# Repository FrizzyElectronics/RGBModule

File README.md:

# RGBModule
The RGB module is a very simple but useful board. It carries a 5050 RGB LED, with a 4pin connector making it easy to add color to your Arduino projects. It's also a great way to learn about the PWM capabilities of Arduino.

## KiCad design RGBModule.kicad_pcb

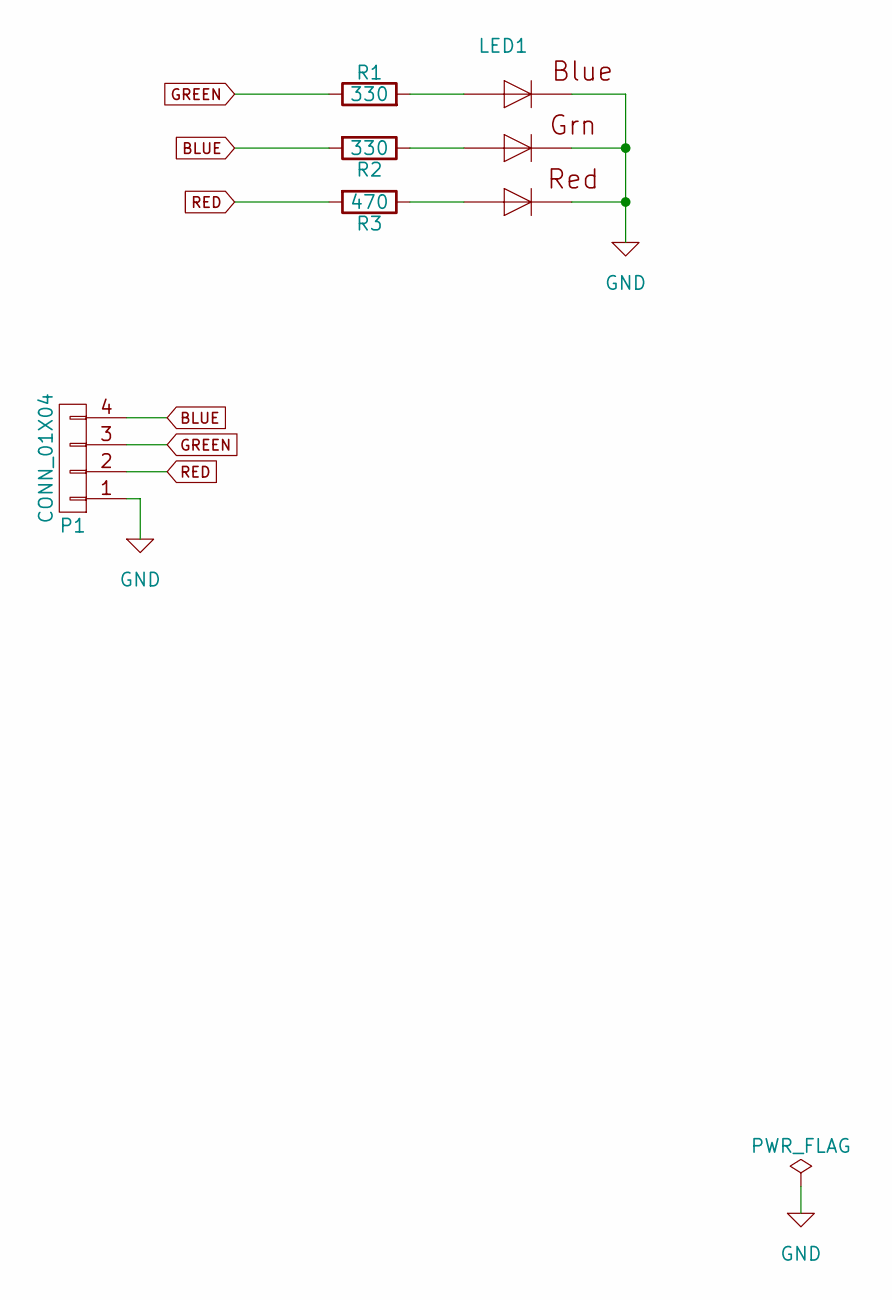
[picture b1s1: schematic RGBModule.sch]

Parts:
LED1: RGBLED5050; LED-TRICOLOR-5050
P1: CONN_01X04; Pin_Header_Angled_1x04_Pitch2.54mm
R1, R2: 330; R_0805
R3: 470; R_0805

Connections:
BLUE: P1.4, R2.2
GND: LED1.4 (BLUE_C), LED1.5 (RED_C), LED1.6 (GREEN_C), P1.1
GREEN: P1.3, R1.1
unnamed: LED1.1 (GREEN_A), R2.1
unnamed: LED1.2 (RED_A), R3.1
unnamed: LED1.3 (BLUE_A), R1.2
RED: P1.2, R3.2

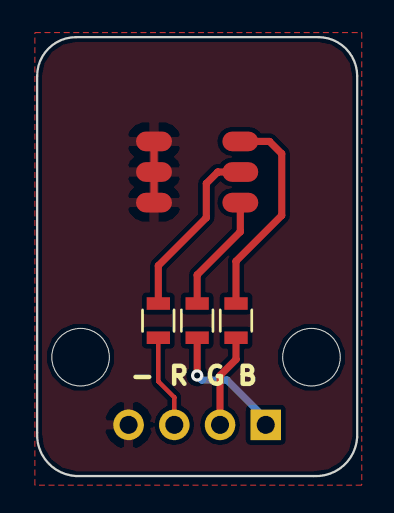
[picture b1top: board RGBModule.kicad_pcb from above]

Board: 2 copper layers, 17.8 x 24.4 mm, 5 parts (0 on the bottom side), 7 nets.

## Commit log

2017-05-22 License Added
2017-05-22 Esquema terminado
2017-05-22 Netlist y footprints asociados
2017-05-22 3D terminado
2017-05-26 Serigrafia añadida
2017-05-26 Añadida la serigrafia en la conexiones
2018-01-20 Gerbers Exportados
    Gerbers exportados para prueba de panelizacion
2018-01-20 Gerbers exportados
    Gerbers exportados para prueba de panelizacion, gm1 a gko
2018-02-12 Logo y conector cambiado
2018-03-03 Alrbol de librerias cambiado, falta 3D
2018-03-04 3D cambiado
2018-03-12 Board render added
2018-03-12 Board image added to Readme
2018-05-06 BOM exportado
2018-05-06 Problema con los colores cambiados
    El verde estaba como B y el azul como G, ya está corregido
2018-05-06 gerbers generados
2018-05-14 Serigrafia del conector cambiada
2018-06-11 PDF generado
2018-07-14 Error de plano de masa solucionado
2018-07-15 Gerbers exportados
